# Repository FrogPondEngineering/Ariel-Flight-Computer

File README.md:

# Ariel-Flight-Computer
Repository for all files needed for the Ariel Flight Computer.
The Ariel Flight Computer Project is released under a GNU General Public License 3.0.

This project is one intended purely for educational uses, and has the final goal of active altitude control of a model rocket.
Air Brake Mechanism Files (.stl) : https://www.thingiverse.com/thing:3795320                                                                                                                                                                                                     

To open Board and schematic files simply drop them into the projects folder in EAGLE and open.

You can find components here:

Terminal Blocks: 
https://www.adafruit.com/product/724

Nano: 
https://www.amazon.com/HiLetgo-ATmega328P-Micro-controller-Development-Compatible/dp/B00E87VWY4/ref=asc_df_B00E87VWY4/?tag=hyprod-20&linkCode=df0&hvadid=312824707815&hvpos=1o5&hvnetw=g&hvrand=9000783748691509949&hvpone=&hvptwo=&hvqmt=&hvdev=c&hvdvcmdl=&hvlocint=&hvlocphy=1024290&hvtargid=pla-645731509584&psc=1

PCB Blanks:
https://www.amazon.com/gp/product/B01MRG7NHC/ref=ppx_yo_dt_b_asin_title_o01_s00?ie=UTF8&psc=1

Ferric Chloride Etching Solution:
https://www.amazon.com/gp/product/B008O9XMYA/ref=ppx_yo_dt_b_asin_title_o02_s00?ie=UTF8&psc=1

BMP280: 
https://www.adafruit.com/product/2651

MPU6050:
https://www.amazon.com/MPU-6050-MPU6050-Accelerometer-Gyroscope-Converter/dp/B008BOPN40/ref=asc_df_B008BOPN40/?tag=hyprod-20&linkCode=df0&hvadid=309773039951&hvpos=1o1&hvnetw=g&hvrand=12526296692438295048&hvpone=&hvptwo=&hvqmt=&hvdev=c&hvdvcmdl=&hvlocint=&hvlocphy=1024290&hvtargid=pla-366166873147&psc=1

Nano 4 pack:
https://www.amazon.com/gp/product/B07DMGM5FT/ref=ppx_yo_dt_b_asin_title_o00_s00?ie=UTF8&psc=1

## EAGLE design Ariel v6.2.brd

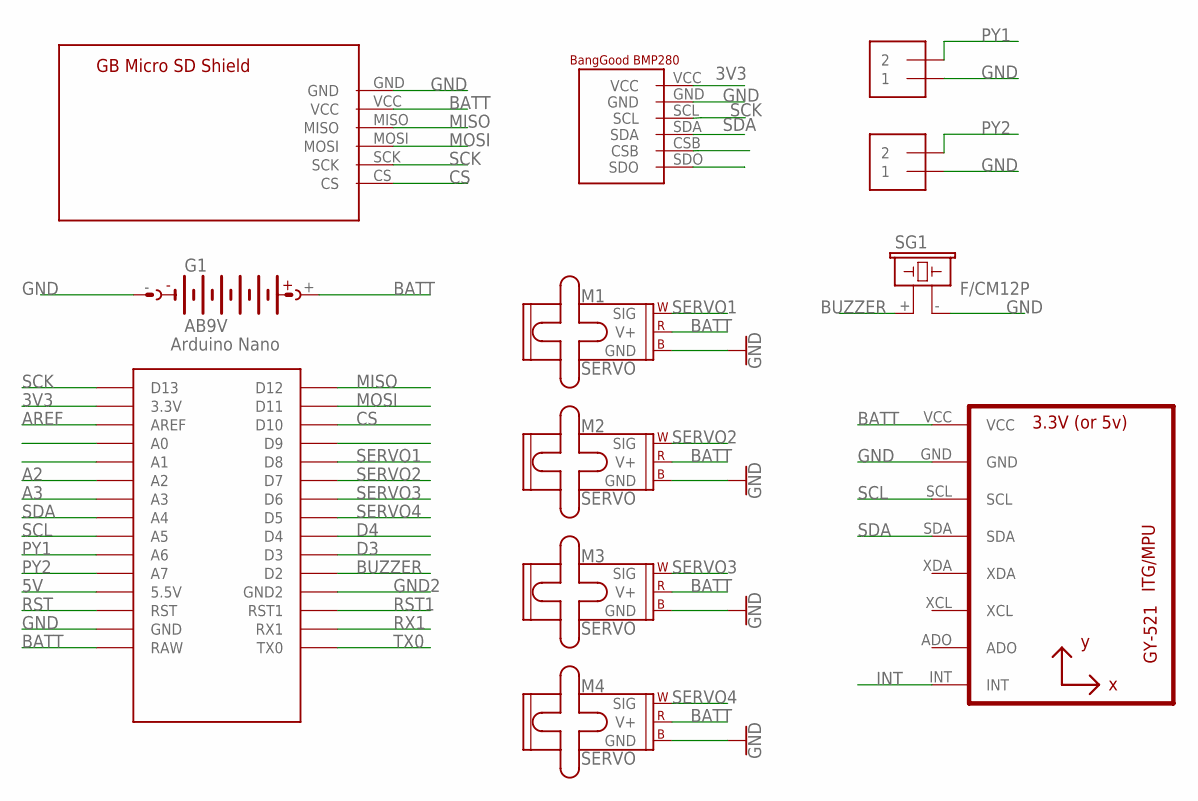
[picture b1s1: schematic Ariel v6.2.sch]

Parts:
G1: AB9V
J1, J2: 1X2-3.5MM
M1, M2, M3, M4: SERVO; 1X03
SG1: F/CM12P
U1: GY-521MPU6050; GY-521
U$1: NANO
U$2: BG_BMP280; 01BG_BMP280
U$3: GBMICROSDSHIELD

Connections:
3V3: U$1.3.3V, U$2.VCC
5V: U$1.5V (5.5V)
A2: U$1.A2
A3: U$1.A3
AREF: U$1.AREF
BATT: G1.+, M1.2 (V+), M2.2 (V+), M3.2 (V+), M4.2 (V+), U1.VCC, U$1.RAW, U$3.VCC
BUZZER: SG1.+ (1), U$1.D2
CS: U$1.D10, U$3.CS
D3: U$1.D3
D4: U$1.D4
GND: G1.-, J1.1, J2.1, M1.3 (GND), M2.3 (GND), M3.3 (GND), M4.3 (GND), SG1.- (2), U1.GND, U$1.GND, U$2.GND, U$3.GND
GND2: U$1.GND1 (GND2)
INT: U1.INT
MISO: U$1.D12, U$3.MISO
MOSI: U$1.D11, U$3.MOSI
PY1: J1.2, U$1.A6
PY2: J2.2, U$1.A7
RST: U$1.RST
RST1: U$1.RST1
RX1: U$1.RX1
SCK: U$1.D13, U$2.SCL, U$3.SCK
SCL: U1.SCL, U$1.A5
SDA: U1.SDA, U$1.A4, U$2.SDA
SERVO1: M1.1 (SIG), U$1.D8
SERVO2: M2.1 (SIG), U$1.D7
SERVO3: M3.1 (SIG), U$1.D6
SERVO4: M4.1 (SIG), U$1.D5
TX0: U$1.TX0

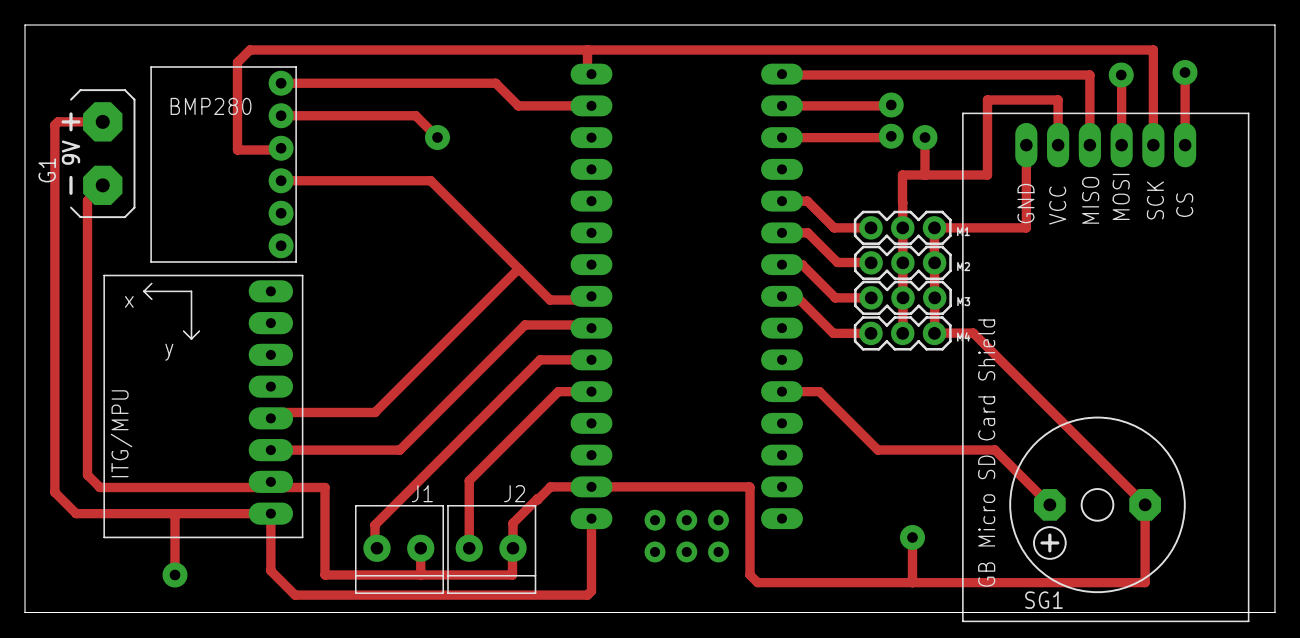
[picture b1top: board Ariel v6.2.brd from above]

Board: 2 copper layers, 100.0 x 47.0 mm, 12 parts (0 on the bottom side), 16 nets.

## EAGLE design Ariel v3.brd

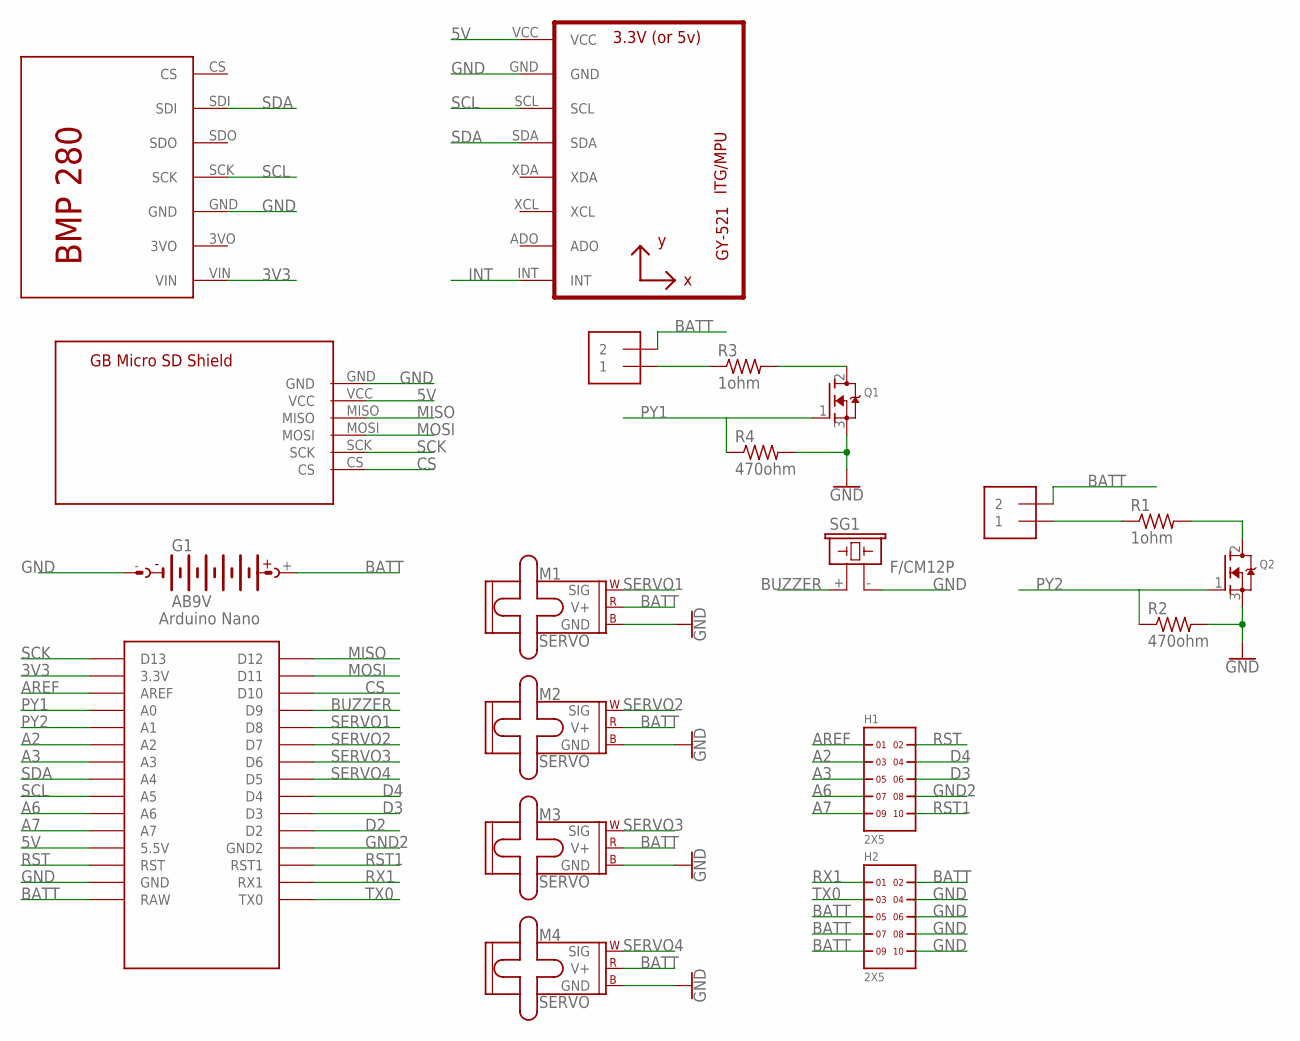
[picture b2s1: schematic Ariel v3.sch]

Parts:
G1: AB9V
H1, H2: 2X5
J1, J2: 1X2-3.5MM
M1, M2, M3, M4: SERVO; 1X03
Q1, Q2: MOSFET-NGDS_TO220V; TO220V
R1, R3: 1ohm; 0805-THM
R2, R4: 470ohm; 0805-THM
SG1: F/CM12P
U1: GY-521MPU6050; GY-521
U$1: NANO
U$2: BMP280
U$3: GBMICROSDSHIELD

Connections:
3V3: U$1.3.3V, U$2.VIN
5V: U1.VCC, U$1.5V (5.5V), U$3.VCC
A2: H1.3, U$1.A2
A3: H1.5, U$1.A3
A6: H1.7, U$1.A6
A7: H1.9, U$1.A7
AREF: H1.1, U$1.AREF
BATT: G1.+, H2.2, H2.5, H2.7, H2.9, J1.2, J2.2, M1.2 (V+), M2.2 (V+), M3.2 (V+), M4.2 (V+), U$1.RAW
BUZZER: SG1.+ (1), U$1.D9
CS: U$1.D10, U$3.CS
D2: U$1.D2
D3: H1.6, U$1.D3
D4: H1.4, U$1.D4
GND: G1.-, H2.4, H2.6, H2.8, H2.10, M1.3 (GND), M2.3 (GND), M3.3 (GND), M4.3 (GND), Q1.3 (S), Q2.3 (S), R2.2, R4.2, SG1.- (2), U1.GND, U$1.GND, U$2.GND, U$3.GND
GND2: H1.8, U$1.GND1 (GND2)
INT: U1.INT
MISO: U$1.D12, U$3.MISO
MOSI: U$1.D11, U$3.MOSI
unnamed: J1.1, R1.1
unnamed: Q2.2 (D), R1.2
unnamed: J2.1, R3.1
unnamed: Q1.2 (D), R3.2
PY1: Q1.1 (G), R4.1, U$1.A0
PY2: Q2.1 (G), R2.1, U$1.A1
RST: H1.2, U$1.RST
RST1: H1.10, U$1.RST1
RX1: H2.1, U$1.RX1
SCK: U$1.D13, U$3.SCK
SCL: U1.SCL, U$1.A5, U$2.SCK
SDA: U1.SDA, U$1.A4, U$2.SDI
SERVO1: M1.1 (SIG), U$1.D8
SERVO2: M2.1 (SIG), U$1.D7
SERVO3: M3.1 (SIG), U$1.D6
SERVO4: M4.1 (SIG), U$1.D5
TX0: H2.3, U$1.TX0

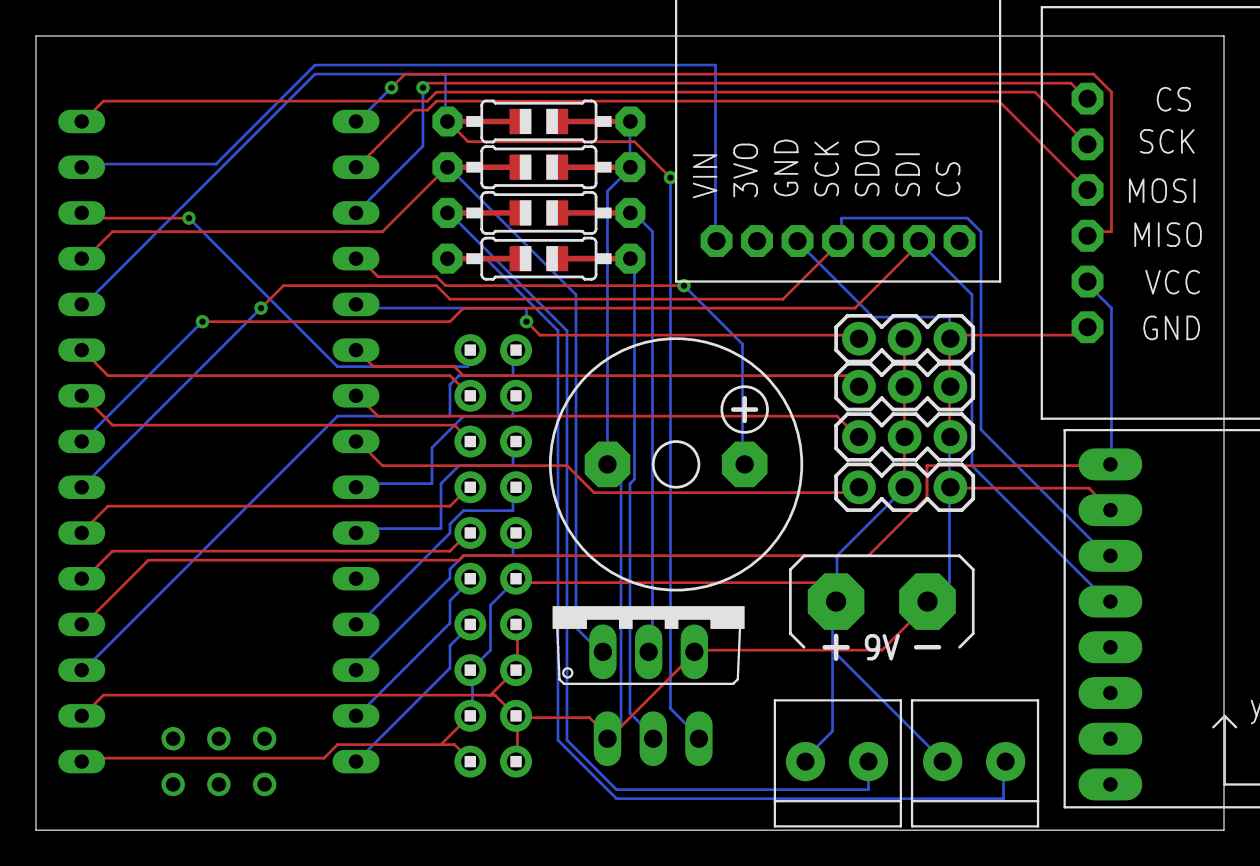
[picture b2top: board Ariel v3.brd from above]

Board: 2 copper layers, 66.0 x 44.1 mm, 20 parts (1 on the bottom side), 33 nets.

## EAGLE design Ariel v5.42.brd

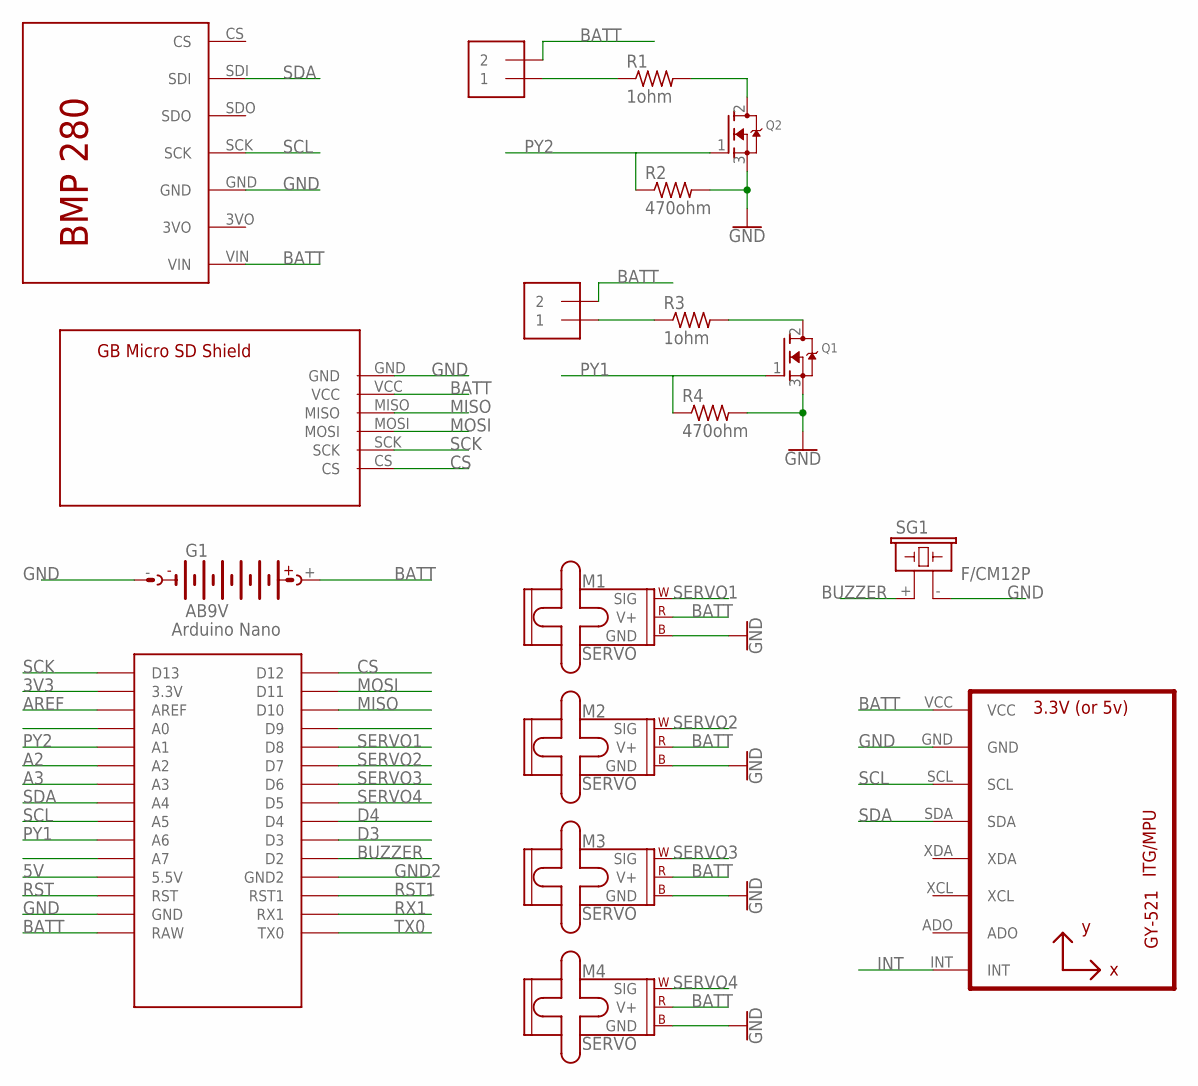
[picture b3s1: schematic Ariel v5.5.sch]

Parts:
G1: AB9V
J1, J2: 1X2-3.5MM
M1, M2, M3, M4: SERVO; 1X03
Q1, Q2: MOSFET-NGDS_TO220V; TO220V
R1, R3: 1ohm; 0805-THM
R2, R4: 470ohm; 0805-THM
SG1: F/CM12P
U1: GY-521MPU6050; GY-521
U$1: NANO
U$2: BMP280
U$3: GBMICROSDSHIELD

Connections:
BATT: G1.+, J1.2, J2.2, M1.2 (V+), M2.2 (V+), M3.2 (V+), M4.2 (V+), U1.VCC, U$1.RAW, U$2.VIN, U$3.VCC
BUZZER: SG1.+ (1), U$1.D2
CS: U$1.D12, U$3.CS
GND: G1.-, M1.3 (GND), M2.3 (GND), M3.3 (GND), M4.3 (GND), Q1.3 (S), Q2.3 (S), R2.2, R4.2, SG1.- (2), U1.GND, U$1.GND, U$2.GND, U$3.GND
INT: U1.INT
MISO: U$1.D10, U$3.MISO
MOSI: U$1.D11, U$3.MOSI
unnamed: J1.1, R1.1
unnamed: Q2.2 (D), R1.2
unnamed: J2.1, R3.1
unnamed: Q1.2 (D), R3.2
PY1: Q1.1 (G), R4.1, U$1.A6
PY2: Q2.1 (G), R2.1, U$1.A1
SCK: U$1.D13, U$3.SCK
SCL: U1.SCL, U$1.A5, U$2.SCK
SDA: U1.SDA, U$1.A4, U$2.SDI
SERVO1: M1.1 (SIG), U$1.D8
SERVO2: M2.1 (SIG), U$1.D7
SERVO3: M3.1 (SIG), U$1.D6
SERVO4: M4.1 (SIG), U$1.D5

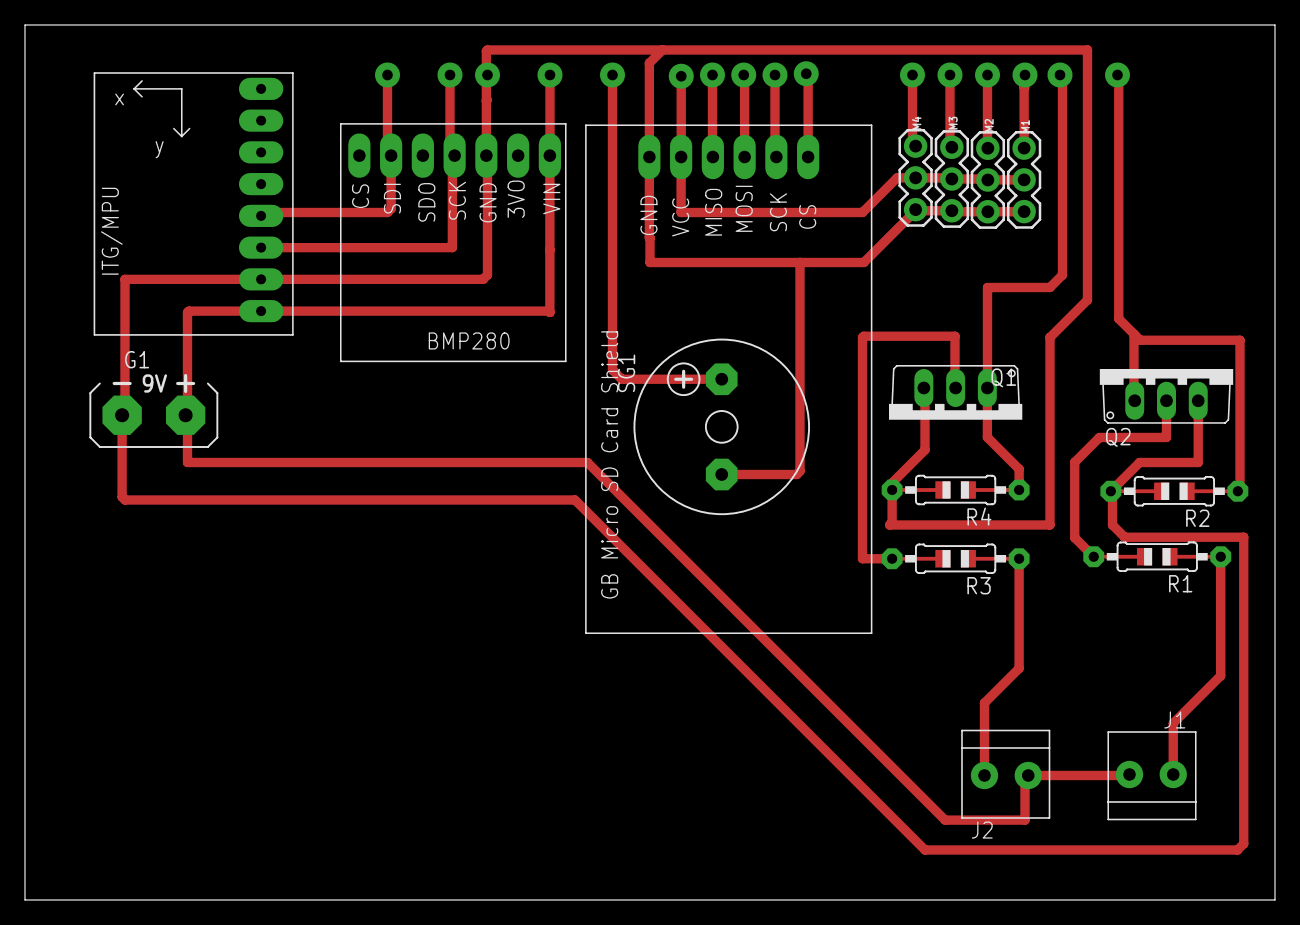
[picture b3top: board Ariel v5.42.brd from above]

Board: 2 copper layers, 100.0 x 70.0 mm, 17 parts (0 on the bottom side), 10 nets.

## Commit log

2019-10-18 Ariel v6.2 Board and Schematic

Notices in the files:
parts and their libraries:
SparkFun-Electromechanical: Licensing: Creative Commons ShareAlike 4.0 International - https://creativecommons.org/licenses/by-sa/4.0
